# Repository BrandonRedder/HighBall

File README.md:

# High Ball  
The MITLL High Ball team’s directive is to design, launch, and control a high altitude balloon (HAB). A control system will use varying wind currents at different altitudes to adjust the balloon’s position. The High Ball team is requesting $1000 for development and testing of a viable HAB control system.

## Team Makeup
### Group Members  
* Mathew Manning
* Brandon Redder
* David Richardson
* David Sanchez
* Kristy Scott
* Kyle Watters

### Project Sponsor and Advisors  
**Sponsor:** MIT Lincoln Laboratories  
**Point of Contact:** Navid Yazdani  

**Primary Advisor:** Dr. Morris Cohen  
**Additional Advisor:** Dr. Whit Smith

## Project Goal
The goal of this project is to develop an altitude and location control system 
for a latex HAB to allow long duration flights over a general location. 
Algorithms take into account current pressure and temperature conditions when 
venting helium or dropping ballast to estimate altitude changes. This will
allow for inexpensive controlled balloon flights for a variety of payloads.

## Libraries
* Pressure Sensor (https://github.com/sparkfun/SparkFun_MS5803-14BA_Breakout_Arduino_Library)
* GPS (https://github.com/sparkfun/SparkFun_I2C_GPS_Arduino_Library)
* TinyGPS++ (http://arduiniana.org/libraries/tinygpsplus/)
* IMU (https://github.com/sparkfun/SparkFun_MPU-9250-DMP_Arduino_Library)

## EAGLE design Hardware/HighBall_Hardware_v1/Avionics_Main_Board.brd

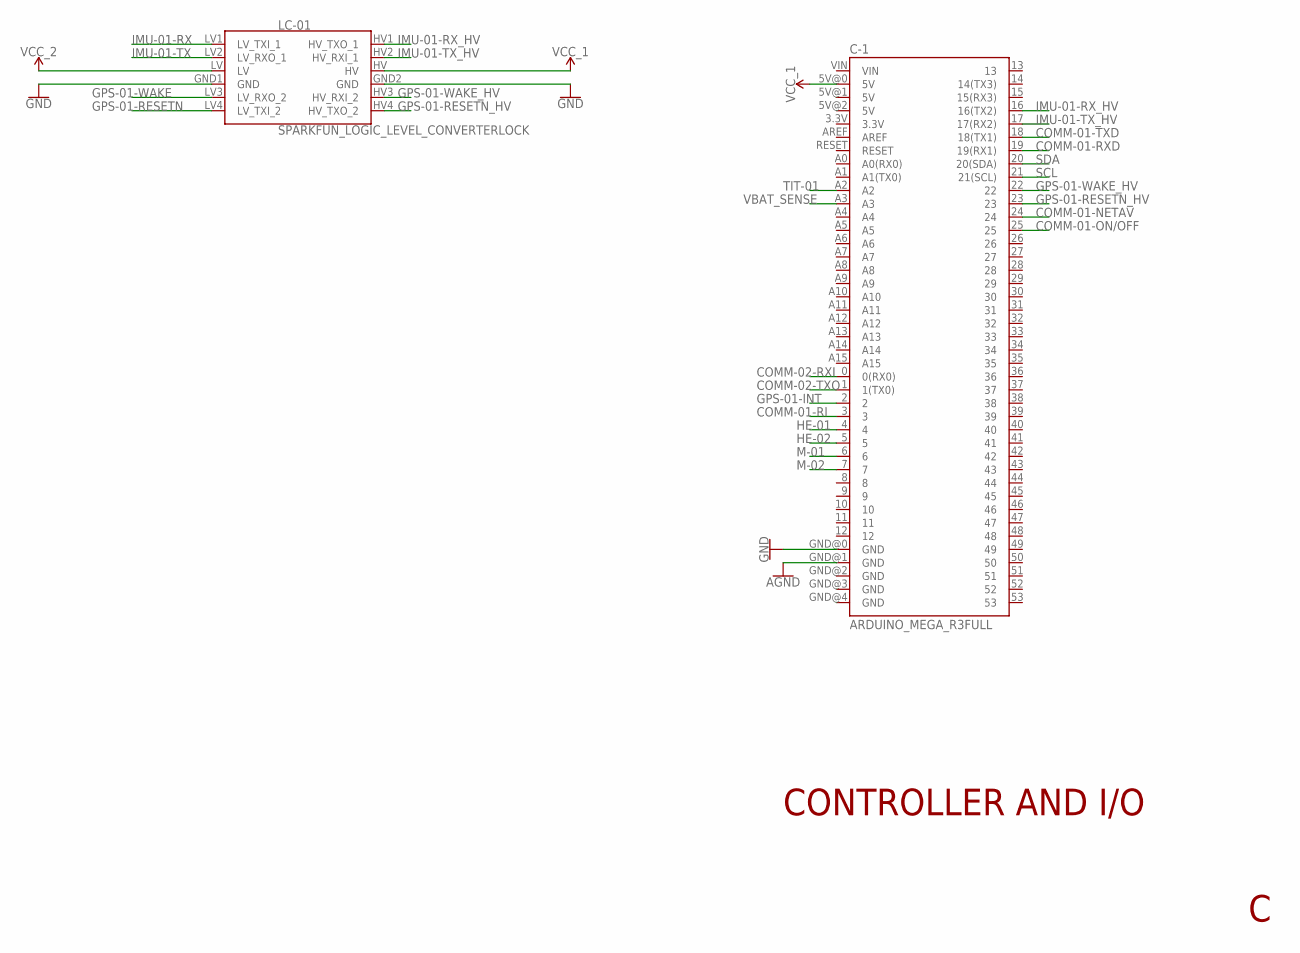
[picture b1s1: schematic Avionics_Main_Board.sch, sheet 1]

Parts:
C-1: ARDUINO_MEGA_R3FULL; ARDUINO_MEGA
LC-01: SPARKFUN_LOGIC_LEVEL_CONVERTERLOCK; SPARKFUN_LOGIC_LEVEL_CONVERTER_LOCK

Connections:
AGND: C-1.GND@1 (GND); also elsewhere on the board
COMM-01-NETAV: C-1.24; also elsewhere on the board
COMM-01-ON/OFF: C-1.25; also elsewhere on the board
COMM-01-RI: C-1.3; also elsewhere on the board
COMM-01-RXD: C-1.19 (19(RX1)); also elsewhere on the board
COMM-01-TXD: C-1.18 (18(TX1)); also elsewhere on the board
COMM-02-RXI: C-1.0 (0(RX0)); also elsewhere on the board
COMM-02-TXO: C-1.1 (1(TX0)); also elsewhere on the board
GND: C-1.GND@0 (GND), LC-01.GND1 (GND), LC-01.GND2 (GND); also elsewhere on the board
GPS-01-INT: C-1.2; also elsewhere on the board
GPS-01-RESETN: LC-01.LV4 (LV_TXI_2); also elsewhere on the board
GPS-01-RESETN_HV: C-1.23, LC-01.HV4 (HV_TXO_2)
GPS-01-WAKE: LC-01.LV3 (LV_RXO_2); also elsewhere on the board
GPS-01-WAKE_HV: C-1.22, LC-01.HV3 (HV_RXI_2)
HE-01: C-1.4; also elsewhere on the board
HE-02: C-1.5; also elsewhere on the board
IMU-01-RX: LC-01.LV1 (LV_TXI_1); also elsewhere on the board
IMU-01-RX_HV: C-1.16 (16(TX2)), LC-01.HV1 (HV_TXO_1)
IMU-01-TX: LC-01.LV2 (LV_RXO_1); also elsewhere on the board
IMU-01-TX_HV: C-1.17 (17(RX2)), LC-01.HV2 (HV_RXI_1)
M-01: C-1.6; also elsewhere on the board
M-02: C-1.7; also elsewhere on the board
SCL: C-1.21 (21(SCL)); also elsewhere on the board
SDA: C-1.20 (20(SDA)); also elsewhere on the board
TIT-01: C-1.A2; also elsewhere on the board
VBAT_SENSE: C-1.A3; also elsewhere on the board
VCC_1: C-1.5V@0 (5V), LC-01.HV; also elsewhere on the board
VCC_2: LC-01.LV; also elsewhere on the board

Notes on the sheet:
CONTROLLER AND I/O

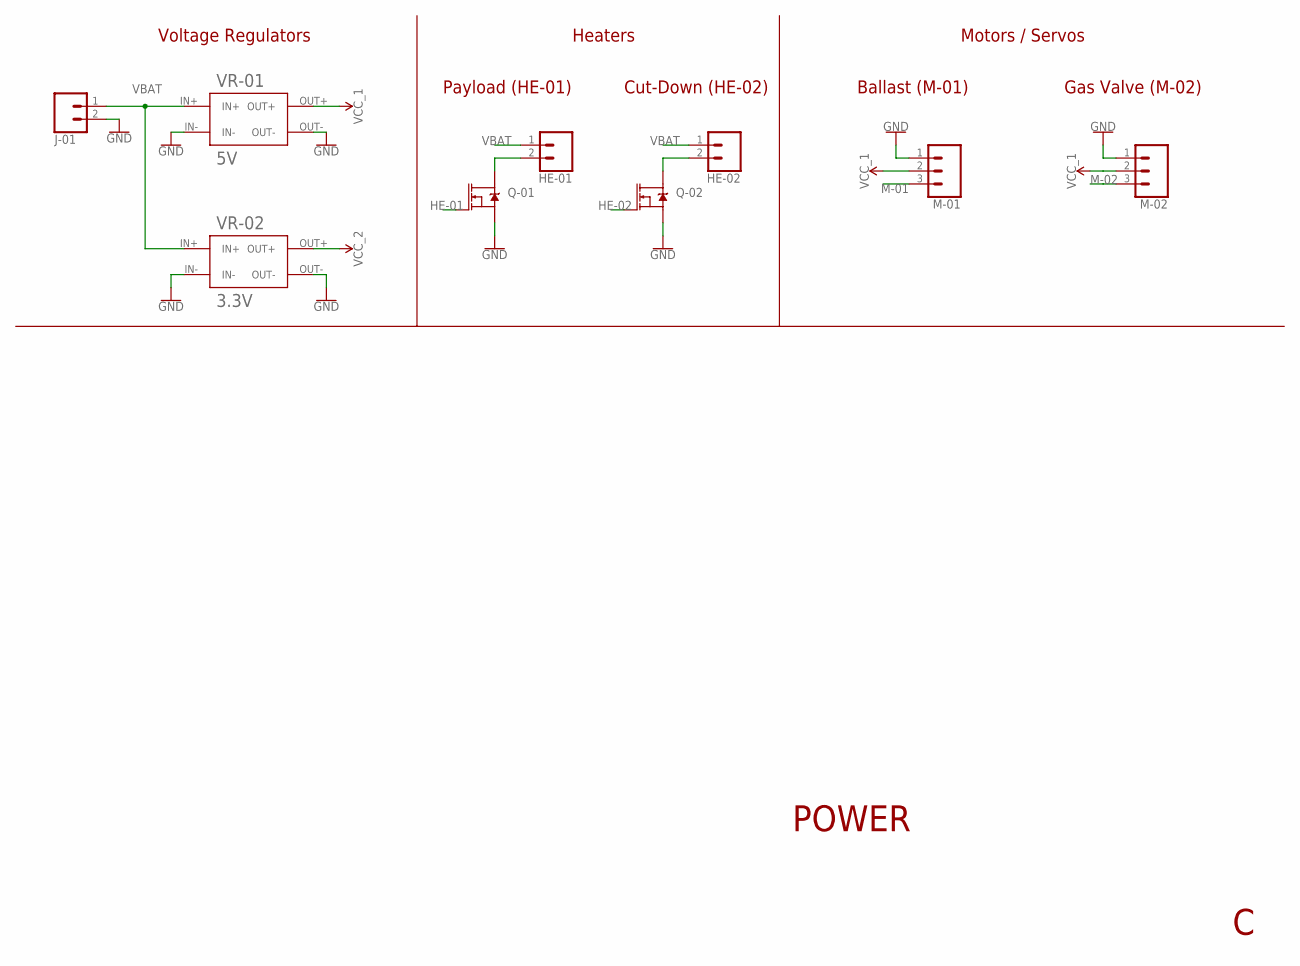
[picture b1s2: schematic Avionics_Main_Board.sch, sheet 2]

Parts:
HE-01, HE-02: CONN_02LOCK; 1X02_LOCK
J-01: CONN_023.5MM_LOCK; SCREWTERMINAL-3.5MM-2_LOCK
M-01, M-02: CONN_03LOCK; 1X03_LOCK
Q-01, Q-02: MOSFET-NCH-FQP30N06L; TO220V
VR-01: 5V; RIORAND_LM2596_BREAKOUT
VR-02: 3.3V; RIORAND_LM2596_BREAKOUT

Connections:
GND: J-01.2, M-01.1, M-02.1, Q-01.3 (S), Q-02.3 (S), VR-01.IN-, VR-01.OUT-, VR-02.IN-, VR-02.OUT-; also elsewhere on the board
HE-01: Q-01.1 (G); also elsewhere on the board
HE-01_OUT: HE-01.2, Q-01.2 (D)
HE-02: Q-02.1 (G); also elsewhere on the board
HE-02_OUT: HE-02.2, Q-02.2 (D)
M-01: M-01.3; also elsewhere on the board
M-02: M-02.3; also elsewhere on the board
VBAT: HE-01.1, HE-02.1, J-01.1, VR-01.IN+, VR-02.IN+; also elsewhere on the board
VCC_1: M-01.2, M-02.2, VR-01.OUT+; also elsewhere on the board
VCC_2: VR-02.OUT+; also elsewhere on the board

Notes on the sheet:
Voltage Regulators
Heaters
Cut-Down (HE-02)
Payload (HE-01)
Motors / Servos
Gas Valve (M-02)
Ballast (M-01)
POWER

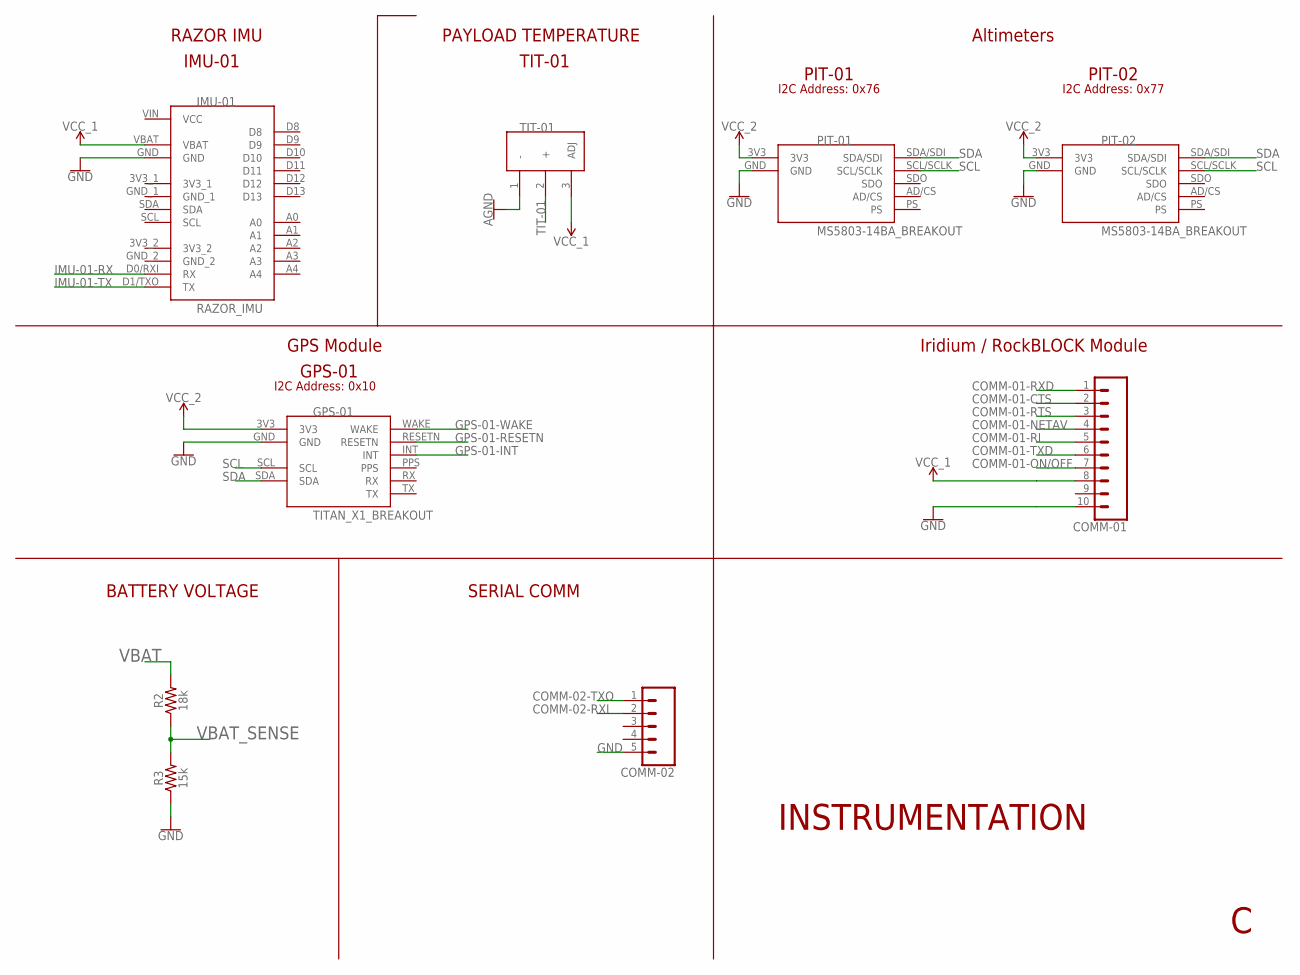
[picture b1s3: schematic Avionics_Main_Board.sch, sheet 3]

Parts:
COMM-01: CONN_10"; 1X10
COMM-02: CONN_05LOCK; 1X05_LOCK
GPS-01: TITAN_X1_BREAKOUT; QWIIC_TITAN_X1_BREAKOUT
IMU-01: RAZOR_IMU
PIT-01, PIT-02: MS5803-14BA_BREAKOUT
R2: 18k; AXIAL-0.3
R3: 15k; AXIAL-0.3
TIT-01: LM335TO-92; TO92

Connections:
5V: TIT-01.3 (ADJ)
AGND: TIT-01.1 (-); also elsewhere on the board
COMM-01-CTS: COMM-01.2
COMM-01-NETAV: COMM-01.4; also elsewhere on the board
COMM-01-ON/OFF: COMM-01.7; also elsewhere on the board
COMM-01-RI: COMM-01.5; also elsewhere on the board
COMM-01-RTS: COMM-01.3
COMM-01-RXD: COMM-01.1; also elsewhere on the board
COMM-01-TXD: COMM-01.6; also elsewhere on the board
COMM-02-RXI: COMM-02.2; also elsewhere on the board
COMM-02-TXO: COMM-02.1; also elsewhere on the board
GND: COMM-01.10, COMM-02.5, GPS-01.GND, IMU-01.GND, PIT-01.GND, PIT-02.GND, R3.P$1 (1); also elsewhere on the board
GPS-01-INT: GPS-01.INT; also elsewhere on the board
GPS-01-RESETN: GPS-01.RESETN; also elsewhere on the board
GPS-01-WAKE: GPS-01.WAKE; also elsewhere on the board
IMU-01-RX: IMU-01.D0/RXI (RX); also elsewhere on the board
IMU-01-TX: IMU-01.D1/TXO (TX); also elsewhere on the board
SCL: GPS-01.SCL, PIT-01.SCL/SCLK, PIT-02.SCL/SCLK; also elsewhere on the board
SDA: GPS-01.SDA, PIT-01.SDA/SDI, PIT-02.SDA/SDI; also elsewhere on the board
TIT-01: TIT-01.2 (+); also elsewhere on the board
VBAT: R2.P$2 (2); also elsewhere on the board
VBAT_SENSE: R2.P$1 (1), R3.P$2 (2); also elsewhere on the board
VCC_1: COMM-01.8, IMU-01.VBAT; also elsewhere on the board
VCC_2: GPS-01.3V3, PIT-01.3V3, PIT-02.3V3; also elsewhere on the board

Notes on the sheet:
RAZOR IMU
IMU-01
PAYLOAD TEMPERATURE
TIT-01
Altimeters
PIT-01
PIT-02
I2C Address: 0x76
I2C Address: 0x77
GPS Module
GPS-01
I2C Address: 0x10
INSTRUMENTATION
Iridium / RockBLOCK Module
BATTERY VOLTAGE
SERIAL COMM

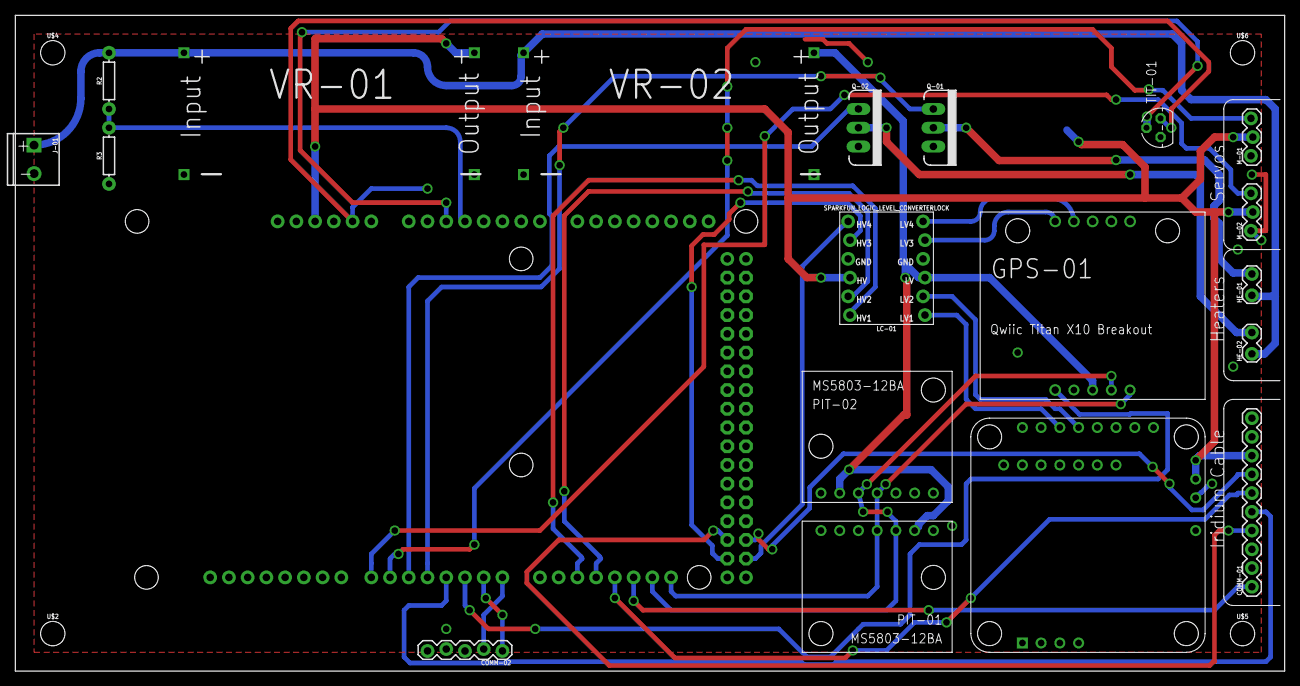
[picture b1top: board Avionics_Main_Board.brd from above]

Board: 2 copper layers, 172.1 x 88.9 mm, 24 parts (1 on the bottom side), 31 nets.

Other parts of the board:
U$2, U$4, U$5, U$6: STAND-OFF

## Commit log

2018-07-23 Initial Commit of Files
2018-08-10 Modifications to Spinner
2018-08-10 Added new header file and code for sensors
    Added Actuators header and cpp. Wrote logic for temperature and pressure transmitters.
2018-08-10 Saved Eagle Changes
2018-08-14 Code and Schematic Updates
    Added State Machine .h & .cpp file
    Added Resistor to LM335 and added battery voltage measurement to schematic.
    Board Layout TBD
2018-08-14 Added GPS Interface code
2018-08-14 Fixed Spacing
2018-08-21 Create Initial README and gitignore
    Added team information to README
    Added tags to gitignore for use with ctags
2018-08-21 Fix README Formatting
    Corrected the README formatting
    Added Project Goal section
2018-08-21 Fix README Formatting
2018-08-21 Update README.md
    Additional Formatting Fixes
    Added initial TODO section
2018-08-21 Initial IMU Code
    setup_IMU_01
    -start and check communication with IMU
    - enable orientation and accelerometer/gyroscope quaternion outputs
    read_IMU_01
    - update values and return magnetometer and quaternion values
    defined IMU_OUTPUT struct to store IMU data
2018-08-21 Update Sensors Files
    Small bugfix for return type of read_PIT_01
    Added function descriptions using numpy docstrings style
    Added TODOC codetags where more explanation is needed
    Added FIXME codetags where I see potential issues
    * Most notable: global variable usage
2018-08-22 Updated license to be for whole team.
    License was automatically generated by Github, modified to reflect whole team.
2018-08-22 Add Include Guards to .h Files
    Added include guards to all .h files
    Added a missing ; on IMU_OUTPUT struct definition
2018-08-24 Fix Sensors.h IMU function declarations
    Original type for read_IMU_01 was void, replaced with IMU_OUTPUT. This
    required moving the IMU_OUTPUT struct declaration before the function
    declaration.
    Added a comment describing the elements contained in the IMU_OUTPUT
    struct.
2018-08-24 Update TODO list in README.md
    Separated the TODO list into smaller tasks. Not a final list.
2018-08-26 Updated 3D Printed files
2018-08-26 Added libraries to readme.md
2018-08-26 Added introduction to readme
2018-08-30 IMU code structure updates
    -new folder for imu code
    -moved code for setup and reading
2018-09-03 Schematic Rev C and CAD Files changes
    Completed rev C of hardware schematic
    Created new PCB layout
    Updated tolerance on ballast dispenser
2018-09-06 Add basic altitude control system
    Created a method for determining when to drop ballast or release helium
    based on current altitude, velocity, and acceleration
    Updated Control.h to reflect the changes made to Control.cpp
    Updated Payload_Main.ino to reflect the changes made to Control.h
2018-09-06 Add velocity and acceleration thresholds
    Added a set_rates function which adjusts the minimum velocity and
    acceleration values that are considered "fast enough"
    Updated the altitude_control function to use the new threshold values
    instead of 0
    Updated the min and max altitudes to use floats instead of integers
    Updated Control.h to reflect the new set_rates function
2018-09-07 Control control code to OOP
    The control algorithm uses an altitude range, as well as thresholds for
    velocity and acceleration in addition to methods to control altitude.
    This lends itself to using a class instead of multiple global variables
    and separate functions.
    Updated Control.h and Control.cpp to use OOP styles
    Moved old Control.h and Control.cpp to *.bak temporarily
2018-09-07 Remove old control files
    Removed the non-OOP based control code.
2018-09-07 Communications
    Initial draft of communication code
2018-09-09 Added Matlab Code
    Flight fimulation and a matlab framework for sending and receiving iridium messages through email.
2018-09-10 Added code to view wind data
2018-09-10 Changes to IMU code
    - Determining orientaiton
    - Projecting acceleration data
    - Determining how much accleration is "up"
2018-09-13 Replace temperature sensor with a class
    Replaced the existing temperature sensor code to contain all
    interactions and required variables within a class.
2018-09-13 correct firmware for imu
    - calculate roll pitch yaw
    - calculate vertical acceleration
    - need to clean up code
2018-09-13 Add class for pressure sensor
    Combined pressure variables and methods into a class. The temperature
    sensor class can be initialized either using the default address of
    sensor 1, an address, or an MS5803 sensor object.
2018-09-14 Horizontal acceleration and direction with relation to north
    - added code to determine horizontal acceration through rotation matrix and projection onto the horizontal plane
    - added code to determine direction with respect to the calibration value (should calibrate so that +x -> N
    -cleaned up code
2018-09-14 Create GPS class
    Replaced all GPS related functionality with a class.
    Created a struct to contain all GPS data for easier access.
2018-09-17 Update to Comm code
    Fixed issues preventing communications code from compiling
2018-09-17 GUI Mockup
    - created GUI mockup
    - does not currently have functionality
    - need to finalize communication code before adding major functionality
2018-09-20 Update control algorithm
    Added parameter weights for calculating the amount of ballast and
    helium to release.
    Adjusted algorithm to use delta altitude, velocity, and acceleration
    Provided access to adjust parameter weights in real time
2018-09-21 Basic Actuator Code
    Rough draft of actuator code
2018-09-27 GUI Bug Fix
    Fast GUI Bug Fix
2018-09-27 Update GUI
    Cahnges to the GUI
2018-10-05 communication with IMU
    - addition of IMU class to sensors.cpp/.h
    - functions to check communication with IMU
    - read data from IMU
    - write data to arduino via serial ports
    - delete functions from main that are not going to be used
2018-10-05 Add altidude calculation to pressure sensor
    Updated the pressure sensor class to include an altitude calculation
    from the baseline.
2018-10-05 Document and update IMU code in Sensors.cpp(.h)
    Added comment blocks to the IMU sensor code to describe functionality.
    Updated the IMU's set_data function to take 3 floats instead of 1
    IMU_Data struct as inputs.
    Created global sensor objects in the main file.
    Read sensor data every iteration of the main loop.
2018-10-11 Writing main loop
    - check current conditions every 5 seconds
    - post processing of conditions (velocity, altitude calculation)
    - run control code every 5 minutes
    - check for manual/automatic mode
2018-10-16 Updated hardware STL files and such
2018-10-16 Website initial commit
2018-10-16 More hardware changes
2018-10-16 Electrical board changes
2018-10-16 Add SerialUSB test to the beginning
2018-10-16 Use SerialUSB instead of Serial
2018-10-16 fix compilation errors
2018-10-16 small changes from merge
2018-10-17 Start Integrating Code
    Began to integrate communications code with main loop
2018-10-25 Edits to fix compilation errors
    - pressure sensors work with this code
    - commented out other sensors
    - need to fix serial prints in constructors
    - fixed pressure sensor addresses
2018-10-25 Remove print statements from constructors
    Constructors were being called before Serial was started, so the print
    statements were failing silently. They were moved to an
    initialize/create function for each sensor to prevent silent failures.
2018-10-25 Fix syntax errors
2018-10-29 Update to Communications
    Fixed encode/decode functions and added new GUI base
2018-10-30 IMU code edits
    - fixed any imu errors
    - added back in commented out imu code
2018-10-30 Revert "Updates to Communication Code"
    This reverts commit 763171ca68bc404786de4f55b44db6b98ac5d0e6, reversing
    changes made to 7ea76f73f2e98c81bf0a484f4f251ebee1ff95d2.
2018-10-31 Communication Update
    Fixes to communication code
2018-11-01 Update IMU serial communication
    Existing communication between the arduino was faulty, so it was replaced with a new communication method.
    The IMU firmware needs to be updated to reflect these changes.
2018-11-01 Update IMU firmware for new communication method
    Add communication code to the IMU firmware to communicate with the
    Arduino
    Add comms test functionality to the IMU firmware to confirm
    communication status
2018-11-01 Update sensor and IMU code to compile
    Small syntax errors in IMU and sensors.cpp were fixed
    Communications was temporarily commented out due to significant
    compilation errors
2018-11-06 Updated GUI
    Added the updated gui
2018-11-07 Added GPS balloon mode
2018-11-07 Update IMU to cast to strings always
2018-11-07 added cutdown code
2018-11-10 Electronics and Hardware changes
2018-11-10 Changed temperatuer sensor to TMP36.
2018-11-10 Added ground for IMU
2018-11-10 Modify cutdown code.
2018-11-10 Add print statement for pressure debugging
2018-11-10 changes from 11/10 gps and imu changs
2018-11-10 Communication and Actuators Update
    Actuator code for servos and newest communications requirements
2018-11-10 Remove IMU dependence
    Comment out IMU requirements
    Add test actuators flag
2018-11-11 Reduce number of pressure.read_pressure() calls
    Moved the call for reading pressure to correspond with reading all the sensor data.
2018-11-11 Add temperature reading to main file
    Temperature was disabled due to changes to the HW. This commit reenables it.
2018-11-11 Patch for Actuators
    Changes actuator setup code
2018-11-11 Ballst Servo Changes
    Use digital 0 for stopped
2018-11-11 11-11 update
    Temp change and communications fix
2018-11-11 Add temperature measurements from pressure sensor
    Temperature sensor was giving incorrect data, so it was replaced with temperature data from the pressure sensor.
2018-11-12 Update cutdown time
    Cutdown was tested and shown to require more than 6 seconds of current.
    The cutdown duration was increased to 40 seconds which was working at
    the last test.
2018-11-16 GUI Changes
    Working GUI
2018-11-17 Stable Communications
    Stable comm code
2018-11-17 GUI update
    GUI update
2018-11-17 Meters to feet
    Meters to feet
2018-11-17 start of poster and final report template
2018-11-25 Added indesign file for poster and basic design.
    Poster still missing some body copy and needs to be proofread before publishing.
2018-12-03 Updates to poster and website
2018-12-03 Added flight data
2018-12-04 Comm. Update
    Added code to retreive weather data CSV files and did final updates of simulation.
2018-12-04 Completed changes to website.
2018-12-04 Final website updates.

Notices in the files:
parts and their libraries:
SparkFun-Boards: Licensing: Creative Commons ShareAlike 4.0 International - https://creativecommons.org/licenses/by-sa/4.0
